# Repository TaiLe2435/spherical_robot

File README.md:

# spherical_robot

This repository is for my research project at Northern Illinois University. We are developing a small-sized omnidirectional spherical robot that will allow for low level control. It is still in its early stages of development.

Currently, there is a working vision tracking system, wireless communication, IMU orientation software, and a V1 robot design. Future work consists of developing a V2 of the robot that is smaller and more robust, as well as developing a control algorithm for the new system.

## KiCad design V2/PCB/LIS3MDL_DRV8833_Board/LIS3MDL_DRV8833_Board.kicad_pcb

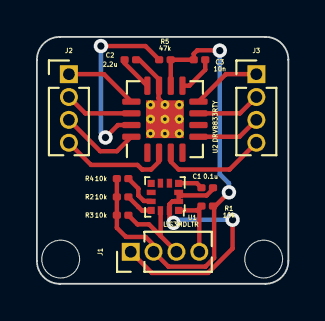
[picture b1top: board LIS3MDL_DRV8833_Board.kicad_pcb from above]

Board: 2 copper layers, 14.0 x 13.7 mm, 15 parts (0 on the bottom side), 18 nets.

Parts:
C1: 0.1u; C_0201_0603Metric
C2: 2.2u; C_0201_0603Metric
C3: 10n; C_0201_0603Metric
H1, H2: MountingHole; MountingHole_2.1mm
J1, J2, J3: Conn_01x04_Male; PinHeader_1x04_P1.27mm_Vertical
R1, R2, R3, R4: 10k; R_0201_0603Metric
R5: 47k; R_0201_0603Metric
U1: LIS3MDLTR; VFLGA-12_2x2mm
U2: DRV8833RTY; Texas_S-PWQFN-N16_EP2.1x2.1mm_ThermalVias

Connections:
/AIN1: J2.1, U2.13 (AIN2)
/AIN2: J2.2, U2.14 (AIN1)
/AOUT1: J2.3, U2.16 (AOUT1)
/AOUT2: J2.4, U2.2 (AOUT2)
/BIN1: J3.1, U2.8 (BIN2)
/BIN2: J3.2, U2.7 (BIN1)
/BOUT1: J3.3, U2.5 (BOUT1)
/BOUT2: J3.4, U2.3 (BOUT2)
/SCL: J1.4, R1.2, U1.1 (SCL/SPC)
/SDA: J1.3, R3.2, U1.11 (SDA/SDI/SDO)
/Vin: C3.2, J1.2, R1.1, R2.1, R3.1, R4.1, R5.1, U2.10 (VM)
GND: C1.2, C2.2, J1.1, U1.2 (RES), U1.3 (GND), U1.12 (RES), U2.11 (GND), U2.17 (GND(PPAD))
unnamed: C1.1, U1.4 (C1)
unnamed: C2.1, U2.12 (VINT)
unnamed: R2.2, U1.10 (CS)
unnamed: R4.2, U1.9 (SDO/SA1)
unnamed: R5.2, U2.15 (nSLEEP)
unnamed: C3.1, U2.9 (VCP)

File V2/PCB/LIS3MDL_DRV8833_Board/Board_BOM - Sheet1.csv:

Id,Designator,Package,Quantity,Designation,Supplier and ref
1,C2,C_0201_0603Metric,1,2.2u,
2,"J2,J3,J1",PinHeader_1x04_P1.27mm_Vertical,3,Conn_01x04_Male,
3,"R1,R2,R4,R3",R_0201_0603Metric,4,10k,
4,U2,Texas_S-PWQFN-N16_EP2.1x2.1mm_ThermalVias,1,DRV8833RTY,
5,C1,C_0201_0603Metric,1,0.1u,
6,"H2,H1",MountingHole_2.1mm,2,MountingHole,
7,R5,R_0201_0603Metric,1,47k,
8,C3,C_0201_0603Metric,1,10n,
9,U1,VFLGA-12_2x2mm,1,LIS3MDLTR,

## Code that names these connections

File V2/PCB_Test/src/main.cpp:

#include <Arduino.h>
#include <iostream>
#include <string>
#include <sstream>
#include <Wire.h> // I2C lib
// #include <LSM6.h> // Accel and Gyro lib
#include <LIS3MDL.h> // Magnetometer lib

// Motor Driver Pins
const int BENBL = 2; //bin1
const int BPHASE = 3; // bin2
const int AENBL = 1; // ain2
const int APHASE = 0; // ain1

// LSM6 gyroAcc; // creating objects
LIS3MDL mag;

float mx, my, mz;

// Function Definition
void move(int uR, int uL);

void setup() 
{
  Serial.begin(115200);
  Serial.println("Hello");

  // MAG Init
  Wire.begin();
  
  if (!mag.init())
   {
     Serial.println("Failed to detect and initialize mag");
     while(1); // preserves error message on serial monitor
   }
  mag.enableDefault();
  mag.read();

}

void loop() 
{
  // get data from mag
  mag.read();
  mx = mag.m.x;
  my = mag.m.y;
  mz = mag.m.z;

  Serial.print(mx);
  Serial.print(' ');
  Serial.print(my);
  Serial.print(' ');
  Serial.println(mz);

  // move motors
  move(80, 80);

}

void move(int uR, int uL) {
  /*
  Am a little confused on control of motor driver. I think aph and bph low then pwm to
  aenbl and benbl makes it move forward then aenbl and benbl low with pwm to phase 
  makes it move backwards. But Aayush just has it hard coded to move forward so idk what.
  Going to test with actual DRV8833 board later.
  */

  // Setting up motor driver
  // digitalWrite(Modepin, HIGH); // turn on
  digitalWrite(APHASE, LOW);   // direction: LOW = forward | HIGH = back
  digitalWrite(BPHASE, LOW);

  // non-blocking
  static unsigned long pulse = 0;

  if(millis() - pulse > 20) {

    analogWrite(AENBL, uR);
    analogWrite(BENBL, uL);
    // Serial.print(uL);
    // Serial.print(' ');
    // Serial.println(uR);
    pulse = millis();

  } 

}

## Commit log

2023-02-14 fixing folders
2023-02-14 Adding IMU program
2023-02-15 added comments
2023-02-15 added unit tests
2023-02-15 CAD files
2023-02-15 added PCB files for new robot
2023-02-18 LP Filter for accelerometer
2023-02-24 Created src and .h file for IMU and fixed bug in QuickI2C
2023-02-28 Added comments for magnetometer calib
2023-03-02 Added V2 pcb tests
2023-03-02 change IMU func from void to float
2023-03-02 added P control
2023-03-05 Fixed QuickI2C lib for V2
2023-03-05 Added more envs to platform.ini
2023-03-06 Added heading P control
2023-03-08 Added blue color detection, and dist and dir functions
2023-03-09 Working feedback loop
2023-03-17 Started on Seeed IMU and BLE tests
2023-03-22 working IMU for V2
2023-04-06 BLE Communication with cpp and py
2023-04-06 Working decoding from hex to dec
2023-04-17 Working BLE with Vision code
2023-04-17 reorganized directories
2023-04-19 Added magnet tracking
2023-04-19 Added keyboard teleop
2023-05-03 created joystick and dpad gui
2023-05-03 added outline to dpad
2023-05-03 added slider unit for RGB values
2023-05-04 Integrated GUI with Robot selection
